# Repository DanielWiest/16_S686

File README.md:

# __**16.S686**__ Closed Loop Frisbee Control
### A Repository of Code, Relevant Documents, and CAD Files

See subsections for more details.

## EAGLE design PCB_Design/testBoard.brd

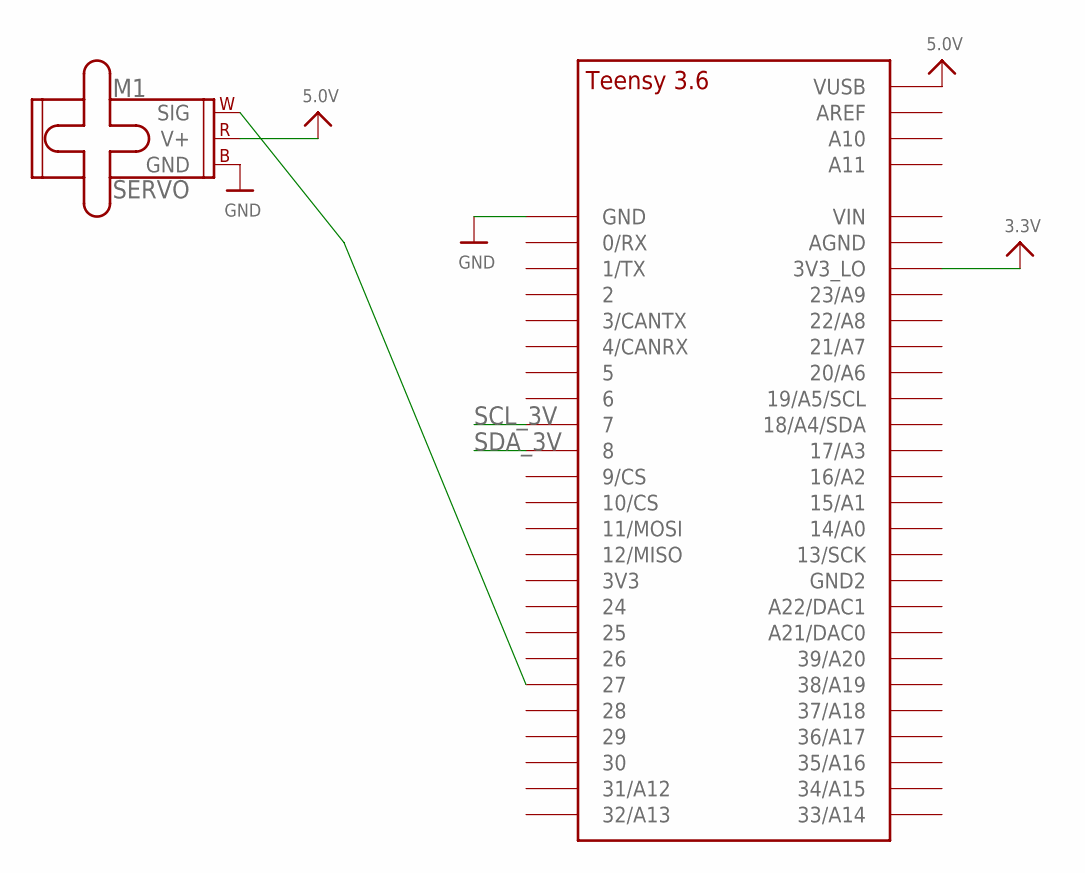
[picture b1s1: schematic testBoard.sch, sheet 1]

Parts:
M1: SERVO; 1X03
U$69: TEENSY_3.5/3.6_BASIC

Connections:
3.3V: U$69.3V3_LO; also elsewhere on the board
5.0V: M1.2 (V+), U$69.VUSB; also elsewhere on the board
GND: M1.3 (GND), U$69.GND; also elsewhere on the board
unnamed: M1.1 (SIG), U$69.27
SCL_3V: U$69.7; also elsewhere on the board
SDA_3V: U$69.8; also elsewhere on the board

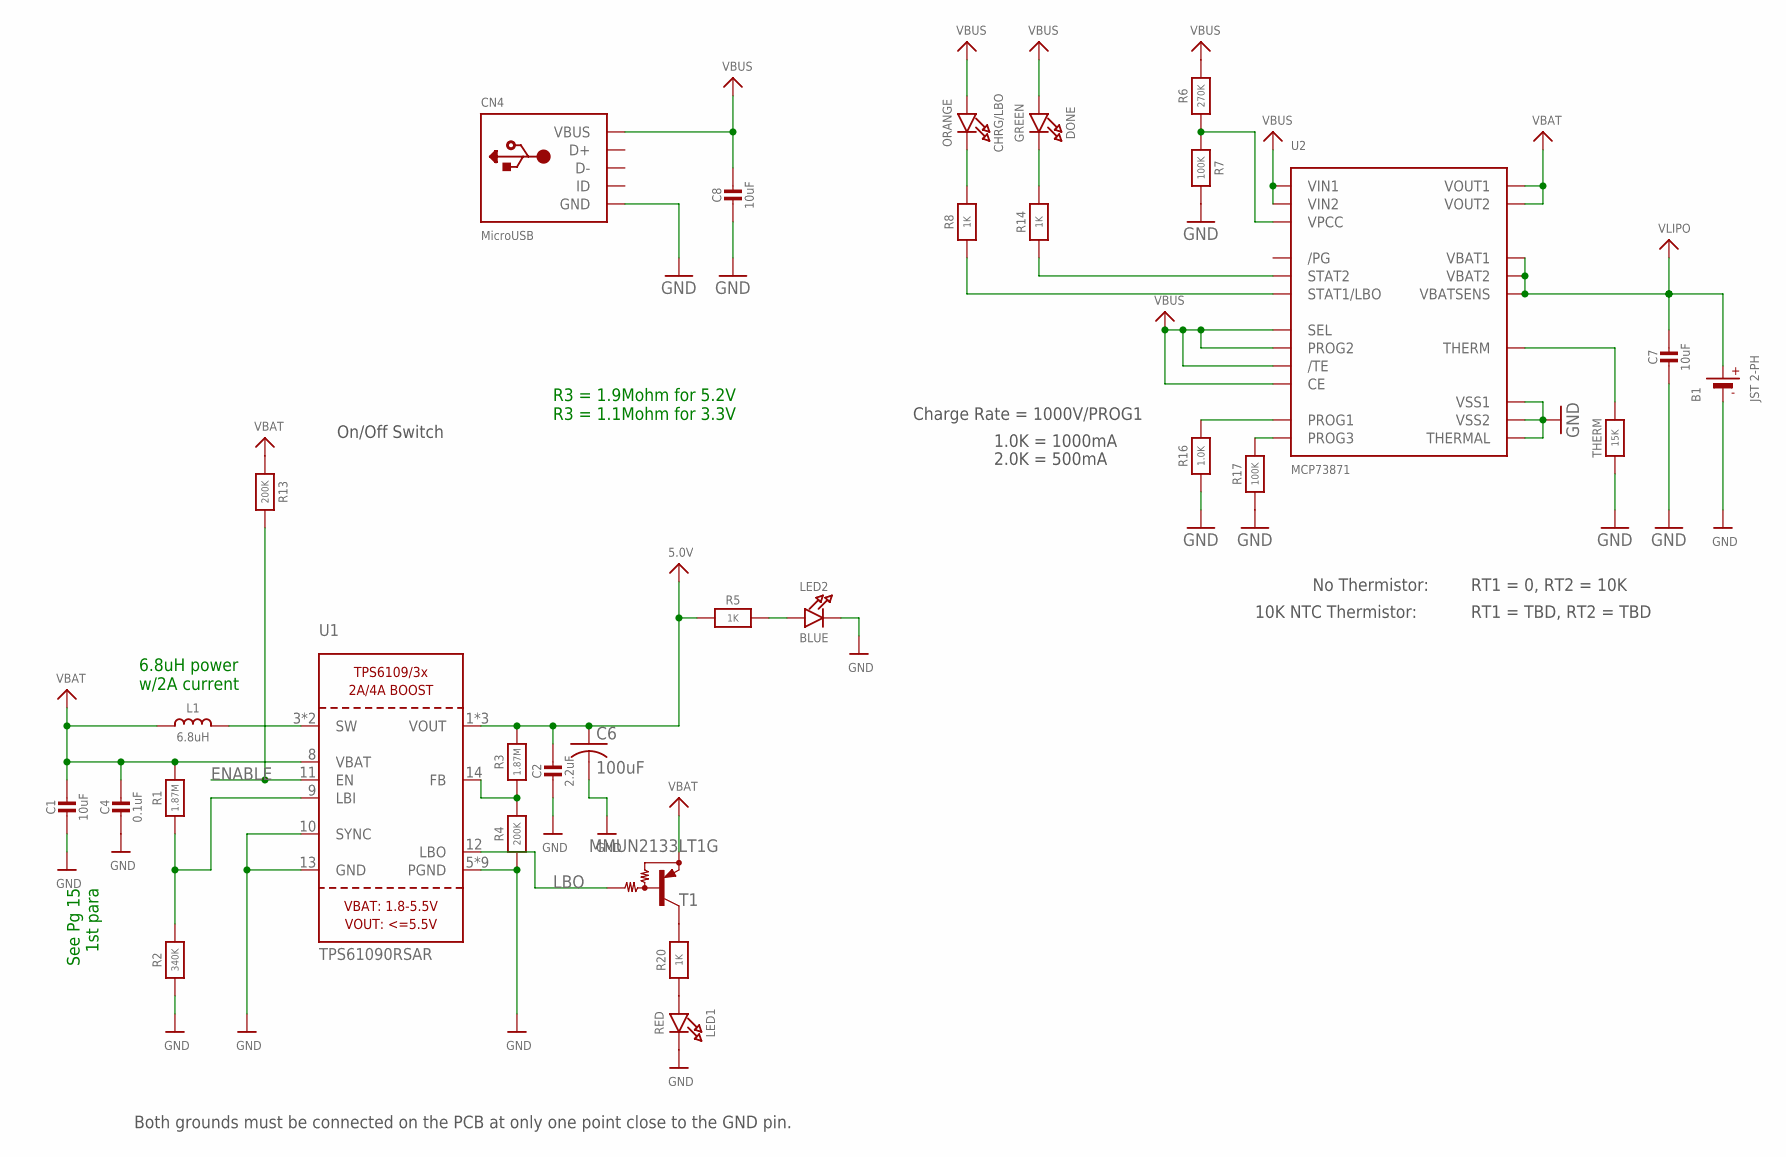
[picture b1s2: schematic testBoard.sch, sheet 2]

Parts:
B1: JST 2-PH; JSTPH2
C1, C7, C8: 10uF; 0805-NO
C2: 2.2uF; 0805-NO
C4: 0.1uF; 0805_10MGAP
C6: 100uF; C1210
CHRG/LBO: ORANGE; CHIPLED_0805_NOOUTLINE
CN4: MicroUSB; 4UCONN_20329
DONE: GREEN; CHIPLED_0805_NOOUTLINE
L1: 6.8uH; INDUCTOR_5X5MM_TDK_VLC5045
LED1: RED; CHIPLED_0805_NOOUTLINE
LED2: BLUE; CHIPLED_0805_NOOUTLINE
R1: 1.87M; _0805MP
R2: 340K; _0805MP
R3: 1.87M; 0805-NO
R4, R13: 200K; 0805-NO
R5, R8, R14, R20: 1K; 0805-NO
R6: 270K; 0805-NO
R7, R17: 100K; 0805-NO
R16: 1.0K; 0805-NO
T1: MMUN2133LT1G; SC59-BEC
THERM: 15K; 0805-NO
U1: TPS61090RSAR; PVQFN-16
U2: MCP73871; QFN20_4MM

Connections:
5.0V: C2.1, C6.1, R3.2, R5.1, U1.1 (VOUT), U1.15 (VOUT), U1.16 (VOUT); also elsewhere on the board
ENABLE: R13.2, U1.11 (EN)
GND: B1.1 (-), C1.2, C2.2, C4.2, C6.2, C7.2, C8.2, CN4.BASE@1 (GND), CN4.BASE@2 (GND), CN4.GND, CN4.SPRT@1 (GND), CN4.SPRT@2 (GND), CN4.SPRT@3 (GND), CN4.SPRT@4 (GND), LED1.C, LED2.C, R2.1, R4.1, R7.2, R16.1, R17.1, THERM.1, U1.5 (PGND), U1.6 (PGND), U1.7 (PGND), U1.10 (SYNC), U1.13 (GND), U1.P$18 (PGND), U1.P$19 (PGND), U1.P$20 (PGND), U1.P$21 (PGND), U1.P$22 (PGND), U1.THERMAL (PGND), U2.P$10 (VSS1), U2.P$11 (VSS2), U2.P$21 (THERMAL); also elsewhere on the board
LBO: T1.B, U1.12 (LBO)
unnamed: L1.P$2 (2), U1.3 (SW), U1.4 (SW)
unnamed: LED1.A, R20.1
unnamed: R1.1, R2.2, U1.9 (LBI)
unnamed: LED2.A, R5.2
unnamed: R3.1, R4.2, U1.14 (FB)
unnamed: R20.2, T1.C
unnamed: R6.1, R7.1, U2.P$2 (VPCC)
unnamed: DONE.C, R14.2
unnamed: R14.1, U2.P$7 (STAT2)
unnamed: THERM.2, U2.P$5 (THERM)
unnamed: R8.1, U2.P$8 (STAT1/LBO)
unnamed: CHRG/LBO.C, R8.2
unnamed: R17.2, U2.P$12 (PROG3)
unnamed: R16.2, U2.P$13 (PROG1)
VBAT: C1.1, C4.1, L1.P$1 (1), R1.2, R13.1, T1.E, U1.8 (VBAT), U2.P$1 (VOUT1), U2.P$20 (VOUT2)
VBUS: C8.1, CHRG/LBO.A, CN4.VBUS, DONE.A, R6.2, U2.P$3 (SEL), U2.P$4 (PROG2), U2.P$9 (/TE), U2.P$17 (CE), U2.P$18 (VIN1), U2.P$19 (VIN2)
VLIPO: B1.2 (+), C7.1, U2.P$14 (VBAT1), U2.P$15 (VBAT2), U2.P$16 (VBATSENS)

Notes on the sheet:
Both grounds must be connected on the PCB at only one point close to the GND pin.
On/Off Switch
See Pg 15 1st para
6.8uH power w/2A current
R3 = 1.9Mohm for 5.2V R3 = 1.1Mohm for 3.3V
Charge Rate = 1000V/PROG1
1.0K = 1000mA
2.0K = 500mA
No Thermistor:
10K NTC Thermistor:
RT1 = 0, RT2 = 10K
RT1 = TBD, RT2 = TBD

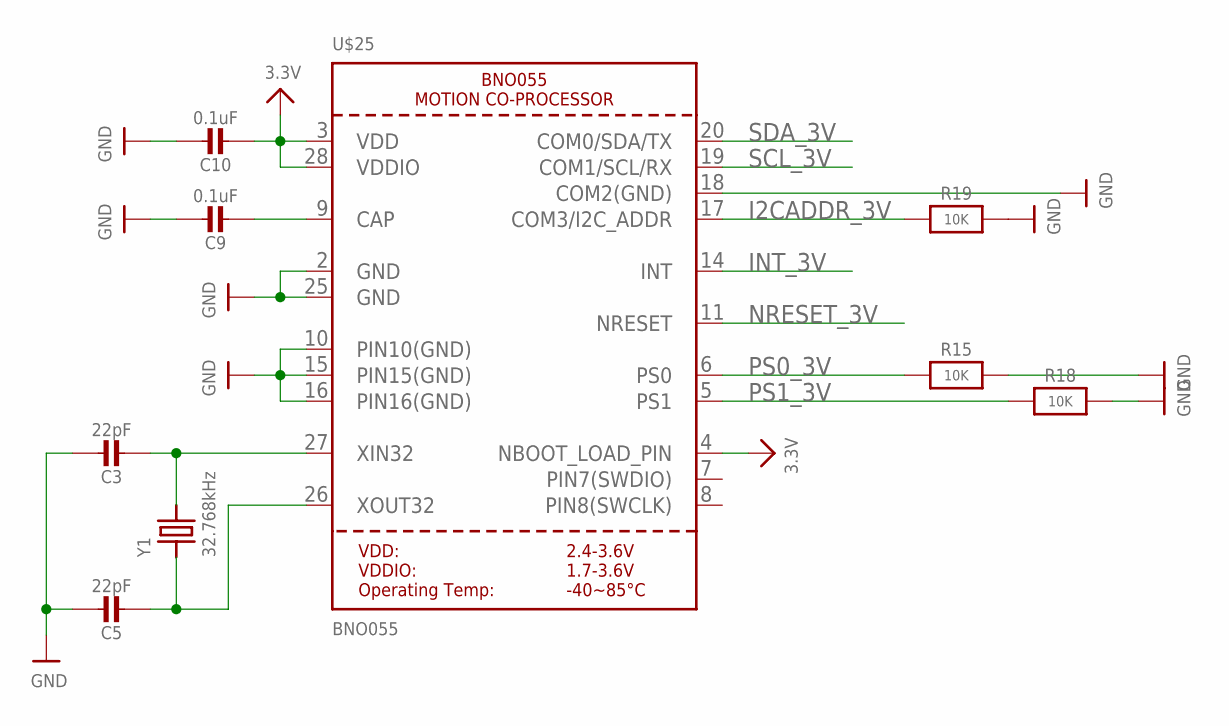
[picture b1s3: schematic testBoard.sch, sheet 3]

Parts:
C3, C5: 22pF; 0805-NO
C9: 0.1uF; 0805-NO
C10: 0.1uF; 0805_10MGAP
R15, R18, R19: 10K; 0805-NO
U$25: BNO055
Y1: 32.768kHz; CRYSTAL_8X3.8

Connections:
3.3V: C10.2, U$25.3 (VDD), U$25.4 (NBOOT_LOAD_PIN), U$25.28 (VDDIO); also elsewhere on the board
GND: C3.1, C5.1, C9.1, C10.1, R15.2, R18.2, R19.2, U$25.2 (GND), U$25.10 (PIN10(GND)), U$25.15 (PIN15(GND)), U$25.16 (PIN16(GND)), U$25.18 (COM2(GND)), U$25.25 (GND); also elsewhere on the board
I2CADDR_3V: R19.1, U$25.17 (COM3/I2C_ADDR)
INT_3V: U$25.14 (INT)
unnamed: C3.2, U$25.27 (XIN32), Y1.P$4 (2)
unnamed: C5.2, U$25.26 (XOUT32), Y1.P$1 (1)
unnamed: C9.2, U$25.9 (CAP)
NRESET_3V: U$25.11 (NRESET)
PS0_3V: R15.1, U$25.6 (PS0)
PS1_3V: R18.1, U$25.5 (PS1)
SCL_3V: U$25.19 (COM1/SCL/RX); also elsewhere on the board
SDA_3V: U$25.20 (COM0/SDA/TX); also elsewhere on the board

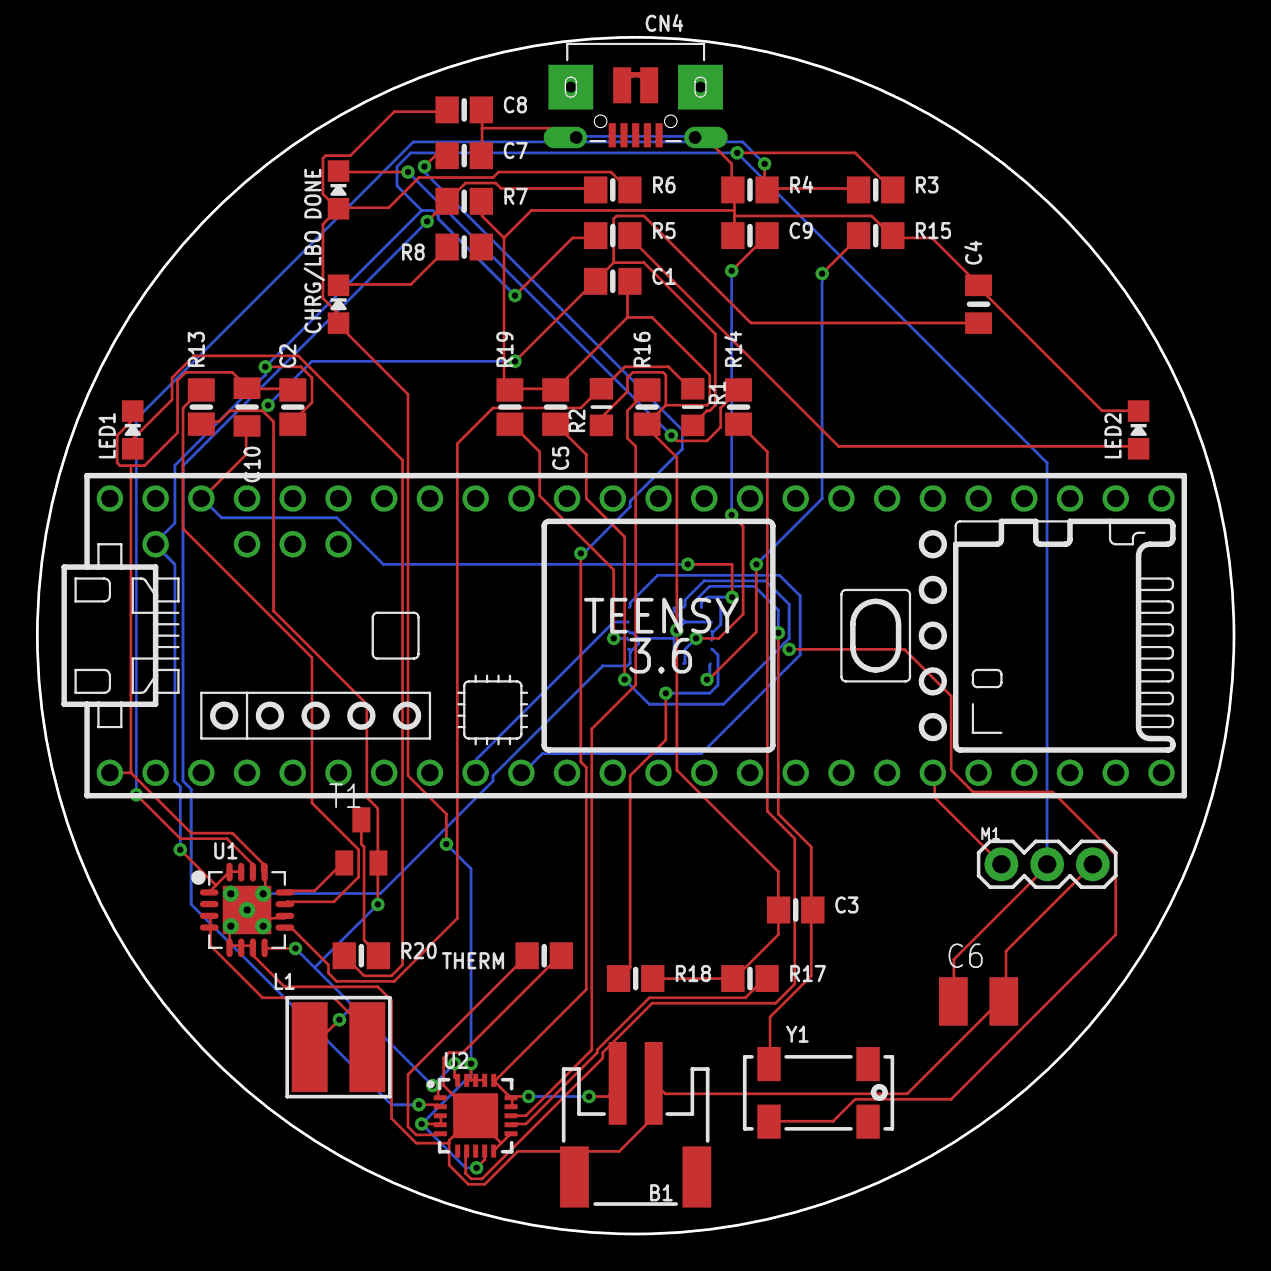
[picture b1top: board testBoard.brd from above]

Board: 2 copper layers, 66.5 x 66.5 mm, 41 parts (1 on the bottom side), 31 nets.

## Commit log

2018-11-26 Adding some pre-existing data
2018-11-26 Continuning to add pre-existing content
2018-11-26 updating current content
2018-11-26 Content Update
2018-11-29 Added dynamic simulation
2018-11-29 fixing references
2018-11-29 new CAD models
2018-11-29 added scripts
2018-12-05 Teensy code updates.
2018-12-05 Added python visualization scripts
2018-12-06 Added more trial data and updated the logging script
2018-12-07 updated CAD
2018-12-07 more state localization work
2018-12-08 Updated code
2018-12-09 Added phase dependent control intensity
2018-12-09 Added circuit schematics
2018-12-10 Code appears to be functional
2018-12-11 Updated main code to reflect a more realistic error value
2018-12-11 Adding the most recent modified sensor libraries
2018-12-13 Adding more local CAD files
2018-12-13 CAD Changes
2018-12-14 Updating cad models
2019-01-12 Adding balanced electronics container draft to be 3d printed.
2019-01-12 Enclosure updates
2019-01-12 nearly finalized enclosure
2019-01-12 A few final changes
2019-01-12 cosmetic tweak
2019-01-13 bugfix
2019-01-13 Final switch dim update
2019-01-16 Added PCB design files.

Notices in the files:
parts and their libraries:
microbuilder: This work is placed in the public domain, and may be freely used for commercial and non-commercial work with the following conditions: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
SparkFun-Electromechanical: Licensing: Creative Commons ShareAlike 4.0 International - https://creativecommons.org/licenses/by-sa/4.0
